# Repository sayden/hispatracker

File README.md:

# WIP hispatracker

An Arduino based project for High Altitude Ballooning. APRS tracker, 2xGPS, temperature and pressure. It still lacks SD logging and an external temperature sensor as the sketch was running out of memory. We are working in a improved version with the atmega1284p-pu to achieve this goals (and maybe some more).

## Sensors and libraries in use

### GPS and Altitude: Ublox Neo6M
We strongly recommend to use SlashDevin's [NeoGPS](https://github.com/SlashDevin/NeoGPS) library for its low memory footprint and awesome documentation. The alternative, TinyGPS is too heavy for most applications in a common Arduino (atmega328p-pu).

Our GPS is the Ublox Neo-6m with a performance of 50.000 meters (yes, 50 km) of altitude, 2.5 meters of accuracy and works at 3.3v

### BMP085 Temperature, altitude and pressure sensor

Good compromise between price and capabilities but with a altitude limit of 9000 meters over the sea (27000 feet). It works at 3.3v

### RF Transmission: Radiometrix HX1

We think that maybe this was a mistake. It has a usable range over 10km and a consumption of 140mA. It has a transmit power of 300mW so you probably need HAM license to use it. Also it works at 5v, being the only module with this voltage needs, it has introduce a need of raising the VIN to, at least 6v so that we provide a regulated supply of 5v to the Radio and 3.3v to the rest of the module. Also it has force us to use a logic level converter to communicate to it. 

The good part is that it was the only able to transmit at 144.800 to use the APRS network. So we can use the network to track our payload with webs like [aprs.fi](http://aprs.fi).

The alternative was to use the NTX2 transmitter. This transmitter is license free with a usable range of 500m (thats a 5% of the power of the HX1). It just transmits on 434.075MHz, 434.650MHz and 458.700MHz so it's not in the APRS network. It has a voltage regulator and you can feed it with 3.3 volts. We'll play with it in the future.

### Arduino Pro Mini 3.3v

Finally, our brain is controlled by an Arduino Pro Mini running at 3.3v

### PCB
Our PCB has been specifically design to fit our needs. You'll find the files in the eagle folder. The PCB has been produce in Seeedstudio. It's 5x5 cm.

### Hardware

Check the [docs](docs) folder. We have used a Prusa i3 3D printer to build the frame of the probe. Basically supports for the batteries, camera, PCB and GPS tracker. STL's will be available in the hardware folder soon as well as in Thingiverse.

The supports are 7x7cm with holes to support the PCB of 5x5cm. In our first tests it reaches a height of 107mm.

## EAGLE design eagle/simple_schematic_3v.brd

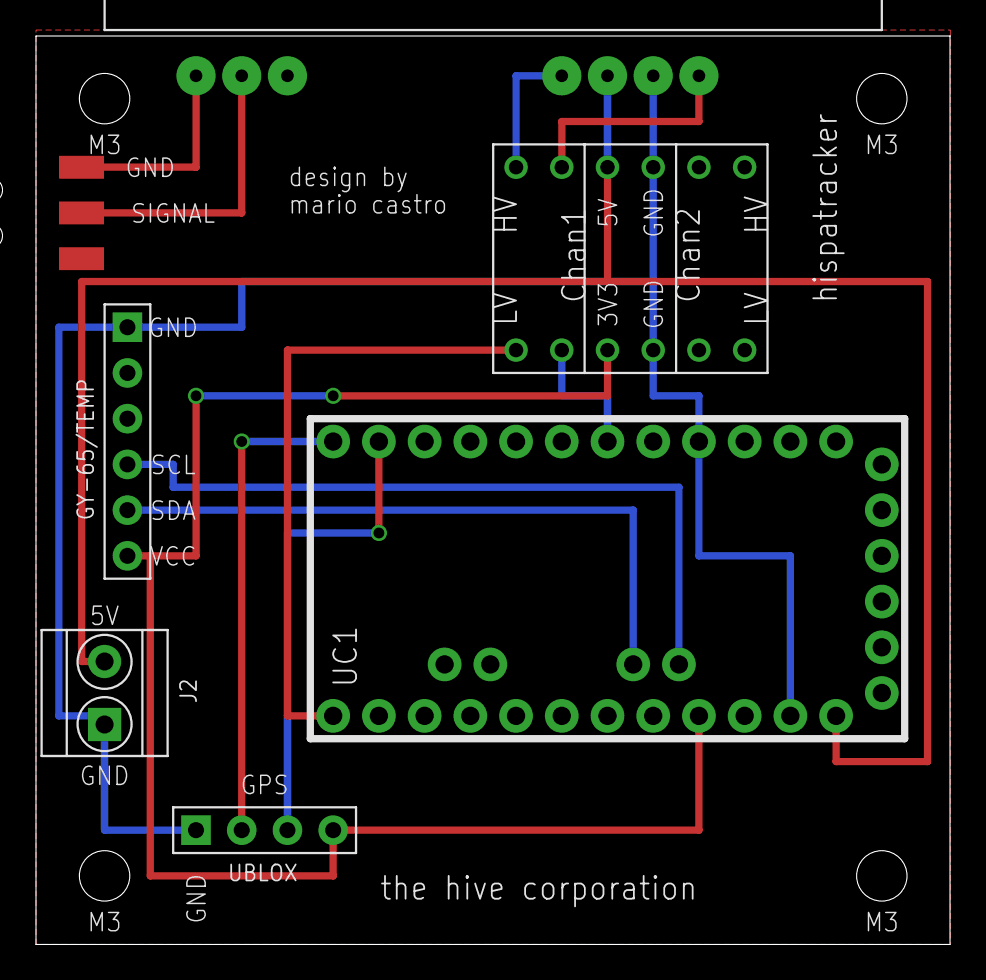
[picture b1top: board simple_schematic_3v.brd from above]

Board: 2 copper layers, 50.8 x 50.5 mm, 7 parts (0 on the bottom side), 13 nets.

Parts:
GY-65/TEMP: 6p-2.54; H6-2.54
J1: 1X03_SMD_RA_MALE_POST_SMALLER
J2: GREEN-2P-3.5; H2-3.5-7.0X7.0MM
U$1: RADIOMETRIX-HX1
U$2: LOGIC_LEVEL_CONVERTER
UBLOX: 4p-2.54; H4-2.54
UC1: ARDUINO_PRO_MINI_3V3; ARDUINO_PRO_MINI

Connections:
3V3: GY-65/TEMP.6, U$2.P$3, UBLOX.4, UC1.21
5V: J2.2, U$1.VCC, U$2.P$10, UC1.24
GND: GY-65/TEMP.1, J2.1, U$1.0V, U$2.P$4, U$2.P$9, UBLOX.1, UC1.4, UC1.23
HX1_ENABLE: U$1.EN, U$2.P$12
HX1_EN_LOW: U$2.P$1, UC1.13
HX1_TXD: U$1.TXD, U$2.P$11
HX1_TXD_LOW: U$2.P$2, UC1.6
unnamed: J1.1, U$1.RFGND2
unnamed: J1.2, U$1.RFOUT
SCL: GY-65/TEMP.4, UC1.A5
SDA: GY-65/TEMP.5, UC1.A4
UBLOX_RX: UBLOX.2, UC1.12
UBLOX_TX: UBLOX.3, UC1.11

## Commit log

2016-06-24 Atomic commit
2016-06-25 Added internal and external temperature sensor
2016-06-26 Configuration cleaned a bit
2016-06-26 APRS message sending working version with SD implementation that doesn't work yet.
2016-06-28 Still doesn't work. I think it's a memory issue
2016-06-28 Minor corrections
2016-06-30 SD Card and external temperature removed. Eagle files added
2016-06-30 GPS Parsing changed to fill APRS format requirements
2016-06-30 Almost working version with APRS message format fixed and more accuracy on extra.
2016-06-30 Trying to make GPS library to work providing more than one update. No luck
2016-07-01 Nothing still
2016-07-01 Complete rewrite of the ino file so that we use NeoGPS as the foundation for this sketch
2016-07-01 EEPROM changed to write APRS appendix 3 table for compressed format.
2016-07-01 Nothing yet :(
2016-07-02 eeprom memory loader moved to a cpp file
2016-07-02 Seems it's working finally.... but consuming a lot of current
2016-07-19 Sheets and planes
2016-07-19 Time spacing defined to 10 seconds until launch day
2016-07-20 README and Eagle files updated. Images uploaded
2016-07-20 Main image resized
2016-07-20 All images resized

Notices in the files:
parts and their libraries:
SparkFun-Boards: Licensing: Creative Commons ShareAlike 4.0 International - https://creativecommons.org/licenses/by-sa/4.0
